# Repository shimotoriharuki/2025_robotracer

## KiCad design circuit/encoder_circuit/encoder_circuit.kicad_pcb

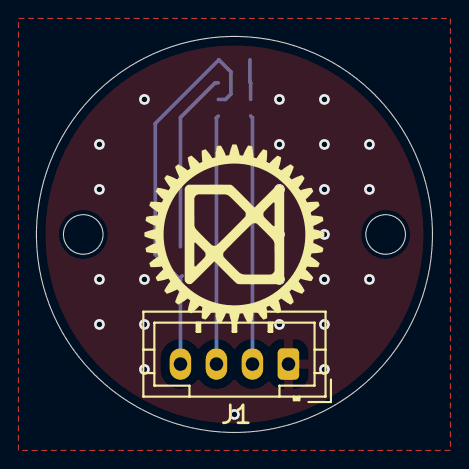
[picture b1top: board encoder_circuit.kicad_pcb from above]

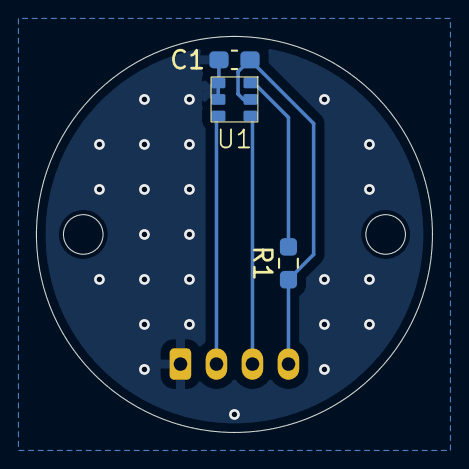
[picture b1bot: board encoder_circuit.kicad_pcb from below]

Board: 2 copper layers, 22.0 x 22.0 mm, 4 parts (3 on the bottom side), 5 nets.

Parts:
C1: 0.1u; C_0603_1608Metric_Pad1.08x0.95mm_HandSolder
J1: Conn_01x04; JST_PH_B4B-PH-K_1x04_P2.00mm_Vertical
R1: 220; R_0603_1608Metric_Pad0.98x0.95mm_HandSolder
U1: NJL5820R

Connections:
+3.3V: C1.1, J1.4, R1.1, U1.5 (Vcc)
GND: C1.2, J1.1, U1.1 (Cathode), U1.2 (GND)
unnamed: J1.2, U1.3 (Vout2)
unnamed: J1.3, U1.4 (Vout1)
unnamed: R1.2, U1.6 (Anode)

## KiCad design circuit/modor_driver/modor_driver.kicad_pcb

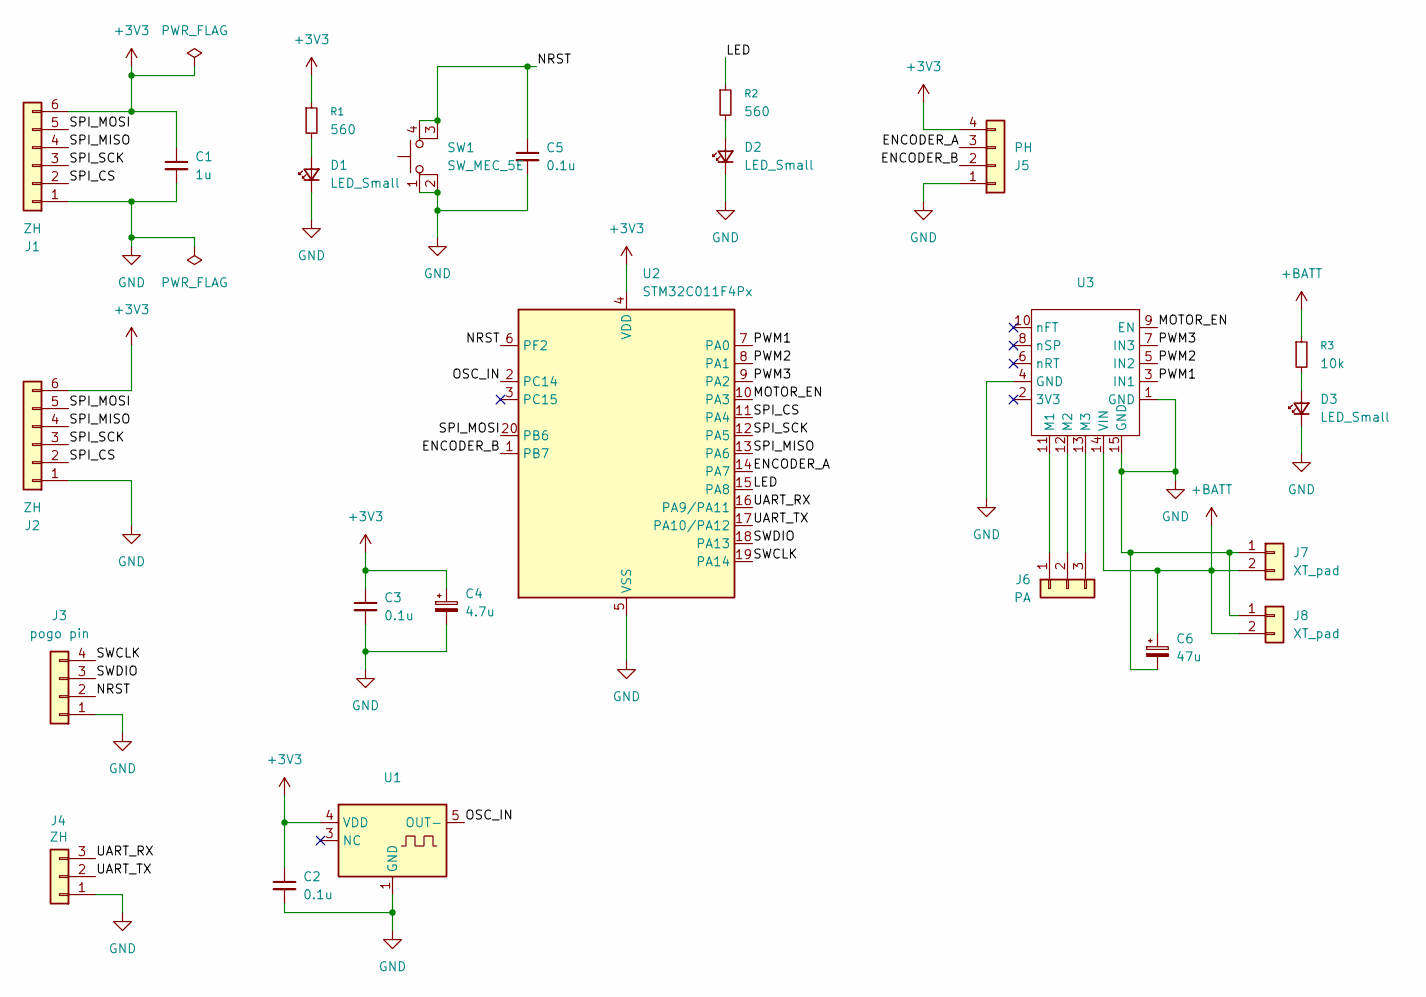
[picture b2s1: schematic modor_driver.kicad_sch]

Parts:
C1: 1u; C_0603_1608Metric_Pad1.08x0.95mm_HandSolder
C2, C3, C5: 0.1u; C_0603_1608Metric_Pad1.08x0.95mm_HandSolder
C4: 4.7u; CP_Radial_D5.0mm_P2.00mm
C6: 47u; CP_Radial_D5.0mm_P2.00mm
D1, D2, D3: LED_Small; LED_0603_1608Metric_Pad1.05x0.95mm_HandSolder
J1, J2: ZH; JST_ZH_B6B-ZR_1x06_P1.50mm_Vertical
J3: pogo pin; Pogo_magnet_1x04_P2.54mm
J4: ZH; JST_ZH_B3B-ZR_1x03_P1.50mm_Vertical
J5: PH; JST_PH_B4B-PH-K_1x04_P2.00mm_Vertical
J6: PA; JST_PA_1x03
J7: XT_pad; AMASS_XT30U-M_1x02_P5.0mm_Vertical
J8: XT_pad; AMASS_XT30U-F_1x02_P5.0mm_Vertical
R1, R2: 560; R_0603_1608Metric_Pad0.98x0.95mm_HandSolder
R3: 10k; R_0603_1608Metric_Pad0.98x0.95mm_HandSolder
SW1: SW_MEC_5E; SKRPACE010
U1: SOT-23-5_HandSoldering
U2: STM32C011F4Px; TSSOP-20_4.4x6.5mm_P0.65mm
U3: SimpleFOCMini

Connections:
+3V3: C1.1, C2.1, C3.1, C4.1, J1.6, J2.6, J5.4, R1.1, U1.4 (VDD), U2.4 (VDD)
+BATT: C6.1, J7.2, J8.2, R3.1, U3.14 (VIN)
/ENCODER_A: J5.3, U2.14 (PA7)
/ENCODER_B: J5.2, U2.1 (PB7)
/LED: R2.1, U2.15 (PA8)
/MOTOR_EN: U2.10 (PA3), U3.9 (EN)
/NRST: C5.1, J3.2, SW1.3 (K), SW1.4 (A), U2.6 (PF2)
/OSC_IN: U1.5 (OUT-), U2.2 (PC14)
/PWM1: U2.7 (PA0), U3.3 (IN1)
/PWM2: U2.8 (PA1), U3.5 (IN2)
/PWM3: U2.9 (PA2), U3.7 (IN3)
/SPI_CS: J1.2, J2.2, U2.11 (PA4)
/SPI_MISO: J1.4, J2.4, U2.13 (PA6)
/SPI_MOSI: J1.5, J2.5, U2.20 (PB6)
/SPI_SCK: J1.3, J2.3, U2.12 (PA5)
/SWCLK: J3.4, U2.19 (PA14)
/SWDIO: J3.3, U2.18 (PA13)
/UART_RX: J4.3, U2.16 (PA9/PA11)
/UART_TX: J4.2, U2.17 (PA10/PA12)
GND: C1.2, C2.2, C3.2, C4.2, C5.2, C6.2, D1.1 (K), D2.1 (K), D3.1 (K), J1.1, J2.1, J3.1, J4.1, J5.1, J7.1, J8.1, SW1.1, SW1.2, U1.1 (GND), U2.5 (VSS), U3.1 (GND), U3.4 (GND), U3.15 (GND)
unnamed: D1.2 (A), R1.2
unnamed: D2.2 (A), R2.2
unnamed: D3.2 (A), R3.2
unnamed: J6.1, U3.11 (M1)
unnamed: J6.2, U3.12 (M2)
unnamed: J6.3, U3.13 (M3)

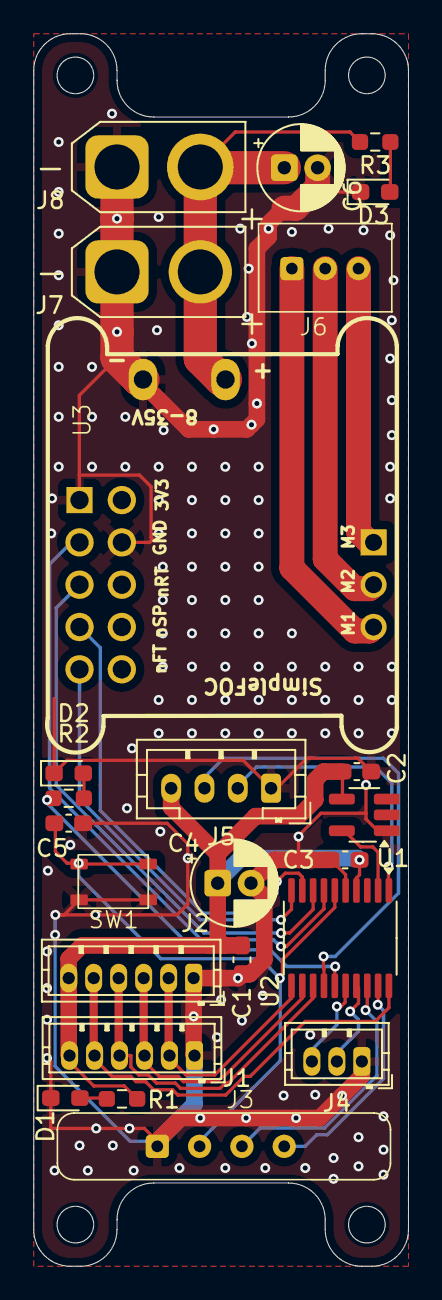
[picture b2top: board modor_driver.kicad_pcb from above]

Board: 2 copper layers, 22.5 x 74.0 mm, 24 parts (0 on the bottom side), 26 nets.

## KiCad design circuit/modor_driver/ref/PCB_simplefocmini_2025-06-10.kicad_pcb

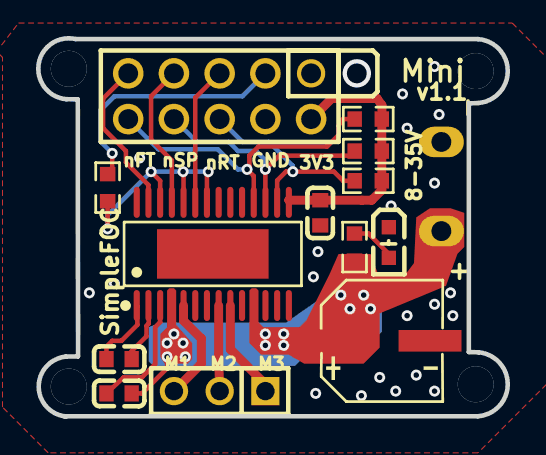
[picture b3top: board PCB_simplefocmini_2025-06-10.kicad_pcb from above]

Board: 2 copper layers, 26.1 x 21.0 mm, 13 parts (0 on the bottom side), 18 nets.

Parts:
C1, C2: 100nF; C0603
C3: 100uF; CAP-SMD_BD6.3-L6.6-W6.6-FD
C4: 470nF; C0603
H1: Female header2.54mm2*5p Straight; HDR-TH_10P-P2.54-V-F-R2-C5-S2.54
LED1: 19-213/Y2C-CQ2R2L/3T(CY); LED0603-R-RD
P1: Header-Female-2.54_1x3; HDR-TH_3P-P2.54-V-F
R1, R2, R3, R4: 10kΩ; R0603
R5: 1kΩ; R0603
U1: DRV8313PWPR; HTSSOP-28_L9.8-W4.5-P0.65-LS6.6-BL-EP

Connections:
3.3V: C4.2, H1.2, R1.1, R2.1, R3.1, U1.15
EN: R4.2, U1.22, U1.24, U1.26
GND: C3.2, C4.1, H1.1, H1.4, LED1.2, U1.6, U1.7, U1.10, U1.12, U1.13, U1.14, U1.20, U1.28, U1.29
IN1: H1.9, U1.27
IN3: H1.5, U1.23
LED1_1: LED1.1, R5.2
NFLT: H1.10, R1.2, U1.18
NRES: H1.6, R3.2, U1.16
NSLP: H1.8, R2.2, U1.17
R4_1: H1.3, R4.1
U1_1: C1.2, U1.1
U1_2: C1.1, U1.2
U1_3: C2.2, U1.3
U1_5: P1.3, U1.5
U1_8: P1.2, U1.8
U1_9: P1.1, U1.9
U1_25: H1.7, U1.25
VCC: C2.1, C3.1, R5.1, U1.4, U1.11

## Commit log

2025-04-29 init
2025-04-29 Create LICENSE
2025-04-29 エンコーダ関係ついか
2025-04-29 シンボルとフットプリントを仮置き
2025-05-16 step
2025-06-07 モタドラ途中
2025-06-08 一旦回路図完成
2025-06-11 レイアウト
2025-06-12 レイアウト変える
2025-06-12 いったんやりきった
2025-06-13 いったん完成
2025-06-15 コネクタ変更とsimplefocminiを修正
2025-06-15 logo追加
2025-06-15 エンコーダ基板の回路図更新
2025-06-15 エンコーダ基板修正
